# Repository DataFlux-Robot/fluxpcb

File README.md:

<div align="center">

<br/>

**English** · [简体中文](README_CN.md)

</div>

---

## ⚡ One prompt. One command. One fab-ready board.

```console
$ flux run projects/stm32n6-px4

  requirements ─▶ spec.yaml ......... ✓ 6 requirements, all mapped
  selection    ─▶ bom.csv ........... ✓ 17 lines, LCSC-verified
  schematic    ─▶ .kicad_sch ........ ✓ kicad-cli ERC: 0 violations
  pcb          ─▶ .kicad_pcb ........ ✓ auto-place + auto-route, DRC: 0
  simulation   ─▶ ngspice MC ×200+3 .. ✓ drop 2.79% ≤ 5% · ripple OK
  firmware     ─▶ ESP-IDF ........... ✓ host-C regression executed

  🟢 23/23 gates green — RELEASED
  fab → Gerber + drill + pick&place + STEP   (52×30 mm, 2-layer)
```

**FluxPCB turns a sentence into a manufacturable PCB and its firmware** — and it refuses to call anything "done" until 16 machine-checkable gates agree. No gate, no glory.

> **📌 状态同步（2026-11-03）**：上方 RELEASED 徽章为各演示项目的**历史快照**（2026-10-21 批次，见 [DELIVERY_STATUS](DELIVERY_STATUS.md) 的撤销与未完成项——含 drc_zero 未绿等待办）。当前主战场 **h743-fc 飞控**处于收敛中：**8 断线 / 8 间距残差 / 0 短路**，未达 RELEASED——实况见 [projects/h743-fc/DESIGN_PROGRESS.md](projects/h743-fc/DESIGN_PROGRESS.md)，里程碑与工件哈希见 [projects/h743-fc/MILESTONES.md](projects/h743-fc/MILESTONES.md)。发布判定已按复审修复：必需阶段全集+证据哈希+导出校验三者齐备才计 RELEASED（局部运行不再冒充发布）。

---

## 🧠 AI proposes. Physics disposes.

LLMs write beautiful netlists — and occasionally invent pin numbers. FluxPCB's rule: **the LLM generates; deterministic solvers and real EDA tools decide.** A failed gate emits structured feedback, the pipeline regenerates, retries are bounded. "Complete" is a physical verdict, not a vibe.

```mermaid
%%{init: {'theme': 'neutral'}}%%
flowchart LR
    A["🗣️ Natural<br/>language"] --> B["📋 spec.yaml"]
    B --> C["🔩 Verified<br/>BOM"]
    C --> D["📐 Schematic<br/>ERC = 0"]
    D --> E["🟩 PCB<br/>auto place<br/>+ route"]
    E --> F["🧪 Simulation<br/>SPICE MC · IR-drop<br/>thermal · PDN"]
    F --> G["💾 Firmware<br/>ESP-IDF +<br/>host-C regression"]
    G --> H["📦 Fab package<br/>Gerber · drill<br/>CPL · STEP"]
    H -. "gate red → structured<br/>feedback → regenerate" .-> B
```

---

## 🚦 16 gates. Zero opinions.

Every artifact is SHA256-stamped. Every verdict links to evidence on disk. A missing tool means `BLOCKED` — **never** a fake pass.

| Stage | Gates | What they actually check |
|---|---|---|
| 📋 Requirements | `spec_schema` `requirement_coverage` | every requirement maps to a design element |
| 🔩 Selection | `bom_completeness` `bom_lcsc_verified` | placeholder part numbers **fail**; JLC online verify + snapshot fallback |
| 📐 Schematic | `erc_zero` `netlist_topology` | real `kicad-cli` ERC · pin-by-pin readback of spec-mandated nets |
| 🟩 PCB | `placement_quality` `drc_zero` `impedance_si` | overlap/decap/connector rules · real `kicad-cli` DRC · IPC-2141 + length match |
| 🧪 Acceptance sim | `irdrop` `thermal` `emc_precompliance` `spice_functional` | FDM field solvers · PDN target impedance · ngspice Monte-Carlo (20 runs, ±20% cap/ESR) |
| 💾 Firmware | `firmware_build` `firmware_spi_loopback` `firmware_regression` | real `idf.py build` when present · the **same** `fw_logic.c` compiled & executed on host |

---

## 🔎 Every conclusion carries its evidence

A finding in FluxPCB is not a string.  It is a `Finding` (`fluxpcb/findings.py`): a stable
**rule id**, **where**, **measured vs limit**, the **assumption it rests on**, a severity
**P0–P3**, a status **confirmed / estimate / unknown**, the **sha256 of the board** it was
measured on, and — when it could not decide — **what information is missing**.

- estimates are capped at P1 *by the type*: they can never outrank a measurement;
- an `unknown` cannot carry a number, and must name its gap;
- the five physics verifiers are no longer stubs: each runs the gates that answer it, and a
  gate that cannot decide yields `unknown`, never a pass;
- each rule has a **mutation that must trip it** (`verifiers/interventions.py`: thin / move /
  short / via_drill / edge → generated → crossed → killed → blind_spot), and a bad board must
  yield strictly more P0+P1 findings than a clean one;
- a fabrication profile is **data with a date and a source** (`mfg/data/jlc_2026-11-25.json`,
  retrieved 2026-11-25) with three tiers and `drop_tier_advice()` — which parameter holds the
  price tier, and what to raise it to;
- knowledge is numbered documents loaded on demand (`K1`–`K30`, five literature surveys, nine
  skills, four prompts), and every LLM call is prefixed with one rule: *when unsure, say so and
  list it as needed information — do not invent a value and reason from it*;
- pages are a product of the data: `flux pages <certs> --boards <dir>` renders one offline
  page per board (open connections, blocking pads, via sites, needed information, ±5 mm copper).

Physics execution (`off / estimate / execute`) defaults to **estimate**; `execute` needs an
explicit confirmation and degrades otherwise.  Method, evidence and limits:
[`fluxpcb/research/SEVEN_PRACTICES_2026-11-25.md`](fluxpcb/research/SEVEN_PRACTICES_2026-11-25.md).

## 📊 PCBWorld-Bench — D3-A 100% · D3-B 100% · D3-C 80%

119 real boards from [PCBWorld](https://github.com/PCBWorld/PCBWorld), 3 independent
runs per board, one criterion: **zero error-severity DRC findings and zero unconnected**.
Full method, controls and limitations: [`fluxpcb/research/PCBWORLD_2026-11-25.md`](fluxpcb/research/PCBWORLD_2026-11-25.md).

| Split | Boards | Ours (cells) | Every run | PCBRouteAgent |
|---|---|---|---|---|
| D3-A | 99 | **297/297 — 100.0%** | 99/99 | 94.9% |
| D3-B | 10 | **30/30 — 100.0%** | 10/10 | 100% |
| D3-C | 10 | **24/30 — 80.0%** | 8/10 | 40% |

Run protocol: 900 s per cell, 6 workers, `FLUXPCB_JAVA_XMX=2g` (without the cap, six un-capped
routers exhaust memory and the two largest boards die without a certificate).  357/357 cells
certified, zero instrument problems, zero crashes.  Code `02a65b3`.

How: measured widening (a real DRC confirms each widened track, and settles the ones that
conflict), a `conflict_reroute` operator that lifts a boxed-in connection anchor-to-anchor and
plans it again — through vias on another layer, or through the copper that closes it (the
conflict set, found by a priced search) — opens repaired by the same operator, a router
retry on timeout, and a 1 mm copper index that took one repair round on a big board from
27 minutes to 72 seconds without changing a single verdict.  Every mechanism ships with
the control that makes it flip.  The pipeline on this path is rule-based: no LLM in it.

2 boards of D3-C remain (`0496`, `0599`); the numbers above are from commit `d90e1a5`.

### 2-layer hybrid engine (2026-11-21): 100% / 0 on both boards

| Board | Connections | Completion | DRC errors | Time | Koppar (baseline) |
|-------|-------------|------------|------------|------|-------------------|
| pic-programmer | 125 | **100%** | **0** | **15.8s** | 100% · 0 · 17s |
| rp2040-minimal | 150 | **100%** | **0** | **34.7s** | 100% · 0 · 11.7s |

Matches Koppar on both boards, and beats its wall clock on pic-programmer; compared with
Freerouting alone, rp2040 rises from 86% / 4 DRC errors to 100% / 0.  Board-true DSN rules
(rp2040: 0.127 mm), project snapshot/restore, and the seven repair operators did the work.

### Older run: 8-board NCER study (2026-10, superseded)

| Board | Layers | Connections | Completion | DRC | Time | Koppar (baseline) |
|-------|--------|-------------|------------|-----|------|-------------------|
| pic-programmer | 2 | 125 | **98.9%** | 378 | 124s | 100% · 0 DRC · 17s |
| rp2040-minimal | 2 | 150 | 70.9% | 0 | 528s | 100% · 0 DRC · 12s |
| pico-vga | 4 | 180 | — | — | — | 100% · 0 DRC · 15s |
| cm5io | 4 | 431 | — | — | — | 100% · 0 DRC · 542s |
| rk3328-som-evb | 4 | 462 | — | — | — | 100% · 0 DRC · 66s |
| scalenode-cm4 | 4 | 446 | — | — | — | 100% · 0 DRC · 161s |
| stmp157-som-evb | 4 | 905 | — | — | — | 100% · 0 DRC · 1068s |
| imx8mp-som-evb | 4 | 997 | — | — | — | 100% · 0 DRC · 1082s |

**Key findings:**
- ✅ **98.9% completion** on pic-programmer (2-layer, 125 connections)
- ✅ **geomir-based clearance checking** for DRC-aware routing
- ✅ **Optimistic grid** (LazySP pattern) for congestion handling
- ⚠️ **378 DRC violations** remaining (mainly track_dangling)
- 📈 **Active development**: targeting 0 DRC + 100% completion

**Compared to baselines:**
- **Koppar**: 100% completion, 0 DRC (hosted API, server-optimized)
- **Freerouting**: 100% completion, 5 DRC (open-source, Java)
- **FluxPCB**: 98.9% completion, 378 DRC (open-source, Python)

---

## 🖥️ Grounding Map — traceability you can click

Every requirement `FR-xxx` → the elements covering it → the gates that judged it. Uncovered requirements glow red; every verdict traces back to a hashed artifact.

<div align="center">

</div>

```bash
flux dashboard projects    # → http://127.0.0.1:8765 · zero-dependency · offline
```

---

## 🏆 From prompt to fab package

<table>
<tr>
<td width="25%" align="center">
<br/>
<b>stm32h743-px4</b> · H743 PX4 flight controller<br/>
36×36 mm · 6-layer · TFBGA240 from ST XML<br/>
<code>23/23 🟢 RELEASED</code><br/>
<a href="gallery/stm32h743-px4/stm32h743-px4-pcb.zip">⬇ fab package</a> · <a href="gallery/stm32h743-px4/prompt.md">the prompt</a>
</td>
<td width="25%" align="center">
<br/>
<b>stm32n6-px4</b> · PX4 flight controller<br/>
55×28 mm · <b>6-layer</b> · TFBGA264 from ST XML<br/>
<code>23/23 🟢 RELEASED</code><br/>
<a href="gallery/stm32n6-px4/stm32n6-px4-pcb.zip">⬇ fab package</a> · <a href="gallery/stm32n6-px4/prompt.md">the prompt</a>
</td>
<td width="33%" align="center">
<br/>
<b>esp32s31-mini</b> · fully autonomous<br/>
52×30 mm · 2-layer · auto place + route<br/>
<code>16/16 🟢 RELEASED</code><br/>
<a href="gallery/esp32s31-mini/esp32s31-mini-pcb.zip">⬇ fab package</a> · <a href="gallery/esp32s31-mini/prompt.md">the prompt</a>
</td>
<td width="33%" align="center">
<br/>
<b>esp32s31-dev</b> · Pi-Zero-size flagship<br/>
65×30 mm · 99 pins from the official Espressif datasheet<br/>
<code>23/23 🟢 ERC=0 · DRC=0</code><br/>
<a href="gallery/esp32s31-dev/esp32s31-dev-pcb.zip">⬇ KiCad project</a> · <a href="gallery/esp32s31-dev/prompt.md">the prompt</a>
</td>
</tr>
</table>

---

## 🤖 Drive it from Claude Code

The repo ships the `/fluxpcb` skill (`.claude/commands/fluxpcb.md`):

```
/fluxpcb ESP32-S31 mini dev board, USB-C power, 2×8 header, 1 button, 1 LED
```

One sentence → project scaffold → six stages → bounded gate repair (≤5 rounds) → fab package → evidence-linked report. **Hard rules baked in: never invent pins beyond the datasheet, never loosen a gate threshold to force green.**

> **Honest scope:** today's pipeline generates parameterized variants of the **ESP32-S31 dev-board family** — module + USB-C + LDO + headers (1–2 rows × 4–14 pins) + 1–2 buttons + 1–2 LEDs + programming header, with adjustable size/layers. Outside that family, the skill says so instead of pretending.

---

## 🚀 Quick start

Only **Python ≥ 3.10** is required. Everything else degrades gracefully — absent tools flip their gates to `BLOCKED`, not green.

```bash
pip install -e .

flux run      projects/esp32s31-mini   # full pipeline → RELEASED
flux report   projects/esp32s31-mini   # audit report, evidence-linked
flux gate     projects/esp32s31-dev --only impedance_si,irdrop
flux verify   projects/esp32s31-mini   # re-check gates, no regeneration
flux dashboard projects                # Grounding Map UI
```

| Optional tool | Unlocks |
|---|---|
| KiCad 10+ (`kicad-cli`) | real ERC / DRC verdicts, Gerber/drill/CPL/STEP export |
| Freerouting | batch auto-routing (DSN/SES) |
| ngspice (KiCad-bundled DLL) | LDO transient Monte-Carlo |
| openEMS + gerber2ems | EM-field / S-parameter sign-off *(adapter ready, wiring in progress)* |
| ESP-IDF / hpm-sdk | on-target firmware compile gate |
| LCSC / JLC API | live part & price verification (snapshot fallback) |

Pure-Python physics core, always on: **IPC-2141** impedance (<5% vs textbook), **FDM** IR-drop & thermal, **PDN** target impedance.

---

## 📍 Status

- ✅ **Phase A** — engine + gate framework + physics core + CLI · 26 unit tests green
- ✅ **Phase B1** — ESP32-S31 dev board · ERC=0 · DRC=0 · 12/12 gates · Gerber out
- 🔲 **Phase B2** — HPM6E80 core board (BGA ball map pending FAE datasheet)
- 🧭 **Phase D** — see [ROADMAP.md](ROADMAP.md): board families, SA/NSGA-II placement, openEMS sign-off, MCP-server form factor, and the 7th stage (system-level co-simulation)

## 🕊️ Engineering honesty

- New 2025 parts not yet indexed by LCSC → BOM says *"verify before ordering"*. Placeholders never pass.
- Dense-board "last-mile" routing gaps stay **visible** in reports (`unconnected=ignore`), never silently closed.
- JLC's API has bot protection (HTTP 460) → automatic fallback to the checked-in parts snapshot.

---

<div align="center">

**If FluxPCB saved you a board respin — leave a ⭐. It funds the next gate.**

[Report a bug](https://github.com/DataFlux-Robot/fluxpcb/issues) · [Roadmap](ROADMAP.md) · Apache-2.0 © FluxPCB contributors

</div>

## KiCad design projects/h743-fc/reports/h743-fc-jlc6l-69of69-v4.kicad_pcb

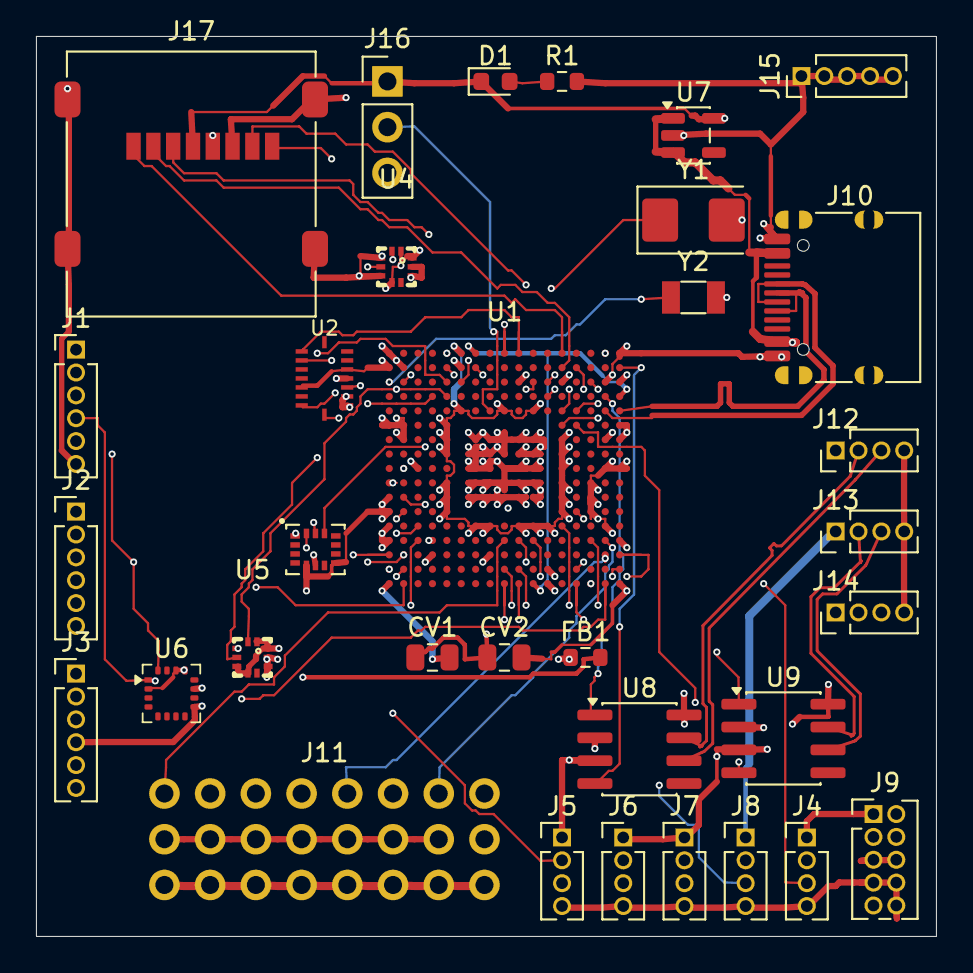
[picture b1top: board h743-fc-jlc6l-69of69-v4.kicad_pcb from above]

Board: 6 copper layers, 50.0 x 50.0 mm, 33 parts (0 on the bottom side), 68 nets.

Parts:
CV1, CV2: 2.2uF; C_0805_2012Metric
D1: BLUE; LED_0603_1608Metric
FB1: 600R@100M; R_0603_1608Metric
J1: GPS; PinHeader_1x06_P1.27mm_Vertical
J2: TELEM1; PinHeader_1x06_P1.27mm_Vertical
J3: TELEM2; PinHeader_1x06_P1.27mm_Vertical
J4: UART_4; PinHeader_1x04_P1.27mm_Vertical
J5: UART_5; PinHeader_1x04_P1.27mm_Vertical
J6: UART_6; PinHeader_1x04_P1.27mm_Vertical
J7: UART_7; PinHeader_1x04_P1.27mm_Vertical
J8: UART_8; PinHeader_1x04_P1.27mm_Vertical
J9: SWD; PinHeader_2x05_P1.27mm_Vertical
J10: USB-C; USB_C_Receptacle_HRO_TYPE-C-31-M-12
J11: PWM; HDR_3x08_P2.54
J12: CAN12; PinHeader_1x04_P1.27mm_Vertical
J13: CAN13; PinHeader_1x04_P1.27mm_Vertical
J14: ADC; PinHeader_1x04_P1.27mm_Vertical
J15: GND; PinHeader_1x05_P1.27mm_Vertical
J16: DEBUG; PinHeader_1x03_P2.54mm_Vertical
J17: microSD; microSD_HC_Molex_47219-2001
R1: 1k; R_0603_1608Metric
U1: STM32H743XIHx; h743_bga
U2: BMI088
U3: LGA14_2P5X3X0P91_IVS; ICM-42688-P
U4, U5: BMP388
U6: IST8310
U7: AP2112K-3.3; SOT-23-5
U8, U9: SN65HVD230; SOIC-8_3.9x4.9mm_P1.27mm
Y1: 24MHz; Crystal_SMD_5032-2Pin_5.0x3.2mm
Y2: 32.768k; Crystal_SMD_3215-2Pin_3.2x1.5mm

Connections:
3V3: D1.1, FB1.1, J4.1, J5.1, J6.1, J7.1, J9.1, J14.1, J16.1, J17.4, U1.A6, U1.B1, U1.C17, U1.E6, U1.E9, U1.E11, U1.F5, U1.F17, U1.G5, U1.G13, U1.G17, U1.H5, U1.H13, U1.J13, U1.K5, U1.K13, U1.L1, U1.L5, U1.L13, U1.M1, U1.M5, U1.M13, U1.N7, U1.N8, U1.N10, U1.N11, U1.N12, U1.P17, U1.U12, U2.3, U2.11, U3.5, U3.8, U4.1, U4.6, U4.10, U5.1, U5.5, U5.6, U5.10, U7.5, U8.3, U8.8, U9.3, U9.8
5V: J1.1, J2.1, J3.1, J8.1, J10.A4, J10.A9, J10.B4, J10.B9, J11.17, J11.18, J11.19, J11.20, J11.21, J11.22, J11.23, J11.24, J12.1, J13.1, U7.1, U7.3
ADC1_INP10: J14.2, U1.L2
ADC1_INP11: J14.3, U1.M2
BOOT0: J16.2, U1.E8
CAN1_H: J12.2, U8.7
CAN1_L: J12.3, U8.6
CAN2_H: J13.2, U9.7
CAN2_L: J13.3, U9.6
FDCAN1_RX: U1.B17, U8.4
FDCAN1_TX: U1.D16, U8.1
FDCAN2_RX: U1.A5, U9.4
FDCAN2_TX: U1.B5, U9.1
GND: CV1.2, CV2.2, J1.6, J2.4, J2.5, J2.6, J3.4, J3.5, J3.6, J4.4, J5.4, J6.4, J7.4, J8.4, J9.3, J9.5, J9.6, J9.7, J9.8, J9.10, J10.A1, J10.A12, J10.B1, J10.B12, J11.9, J11.10, J11.11, J11.12, J11.13, J11.14, J11.15, J11.16, J12.4, J13.4, J14.4, J15.1, J15.2, J15.3, J15.4, J15.5, J16.3, J17.6, J17.SH, R1.2, U1.A1, U1.A17, U1.B2, U1.B6, U1.C10, U1.C13, U1.C16, U1.F1, U1.F2, U1.G2, U1.G7, U1.G8, U1.G9, U1.G10, U1.G11, U1.G16, U1.H7, U1.H8, U1.H9, U1.H10, U1.H11, U1.J3, U1.J7, U1.J8, U1.J9, U1.J10, U1.J11, U1.J16, U1.J17, U1.K7, U1.K8, U1.K9, U1.K10, U1.K11, U1.K15, U1.L7, U1.L8, U1.L9, U1.L10, U1.L11, U1.L15, U1.M15, U1.N1, U1.N16, U1.P1, U1.R4, U1.R8, U1.T12, U1.U1, U1.U17, U2.4, U2.6, U2.7, U3.6, U4.3, U4.5, U4.8, U4.9, U5.3, U5.8, U5.9, U6.9, U6.11, U7.2, U8.2, U9.2, Y1.2
I2C1_SCL: U1.D5, U4.2, U5.2
I2C1_SDA: U1.D4, U4.4, U5.4
I2C2_SCL: J1.4, U1.P3, U6.1
I2C2_SDA: J1.5, U1.P4, U6.16
IMU1_CS2: U1.B7, U2.5
LED_ACT: D1.2, R1.1
NRST: J9.9, U1.K1
OSC32_IN: U1.C2, Y2.1
OSC32_OUT: U1.C1, Y2.2
OSC_IN: U1.J2, Y1.1
PWM_CH1: J11.1, U1.P9
PWM_CH2: J11.2, U1.P10
PWM_CH3: J11.3, U1.T10
PWM_CH4: J11.4, U1.U10
PWM_CH5: J11.5, U1.R16
PWM_CH6: J11.6, U1.R17
PWM_CH7: J11.7, U1.P16
PWM_CH8: J11.8, U1.P15
SDMMC1_CK: J17.5, U1.C12
SDMMC1_CMD: J17.3, U1.D12
SDMMC1_D0: J17.7, U1.E13
SDMMC1_D1: J17.8, U1.E14
SDMMC1_D2: J17.1, U1.A13
SDMMC1_D3: J17.2, U1.B13
SPI1_MISO: U1.A10, U2.15
SPI1_MOSI: U1.C11, U2.9
SPI1_NSS: U1.A9, U2.14
SPI1_SCK: U1.C6, U2.8
SPI2_MISO: U1.R1, U3.1
SPI2_MOSI: U1.R2, U3.14
SPI2_NSS: U1.A16, U3.12
SPI2_SCK: U1.P11, U3.13
SWCLK: J9.4, U1.B14
SWDIO: J9.2, U1.C15
UART4_RX: J5.3, U1.T2
UART4_TX: J5.2, U1.T1
UART5_RX: J8.3, U1.T14
UART5_TX: J8.2, U1.U14
UART7_RX: J6.3, U1.U9
UART7_TX: J6.2, U1.T9
UART8_RX: J7.3, U1.M14
UART8_TX: J7.2, U1.N13
USART1_RX: J1.3, U1.C5
USART1_TX: J1.2, U1.U15
USART2_RX: J2.3, U1.U2
USART2_TX: J2.2, U1.N3
USART3_RX: J3.3, U1.T17
USART3_TX: J3.2, U1.U16
USART6_RX: J4.3, U1.F13
USART6_TX: J4.2, U1.F14
USB_DM: J10.A7, J10.B7, U1.E17
USB_DP: J10.A6, J10.B6, U1.E16
VCAP: CV1.1, CV2.1, U1.A7, U1.D17, U1.U11
VDDA: FB1.2, U6.2, U6.13, U6.14

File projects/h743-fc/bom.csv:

ref,mpn,lcsc,footprint,datasheet,value,role,package,verified,verify_note,alternatives
U1,STM32H743XIHx,,flux:H743_BGA,https://www.st.com/resource/en/datasheet/stm32h743xi.pdf,STM32H743XIHx,mcu_h743,TFBGA240,False,PX4系列器件C号下单前核实,[]
U2,BMI088,,flux:BMI088,https://www.bosch-sensortec.com/media/boschsensortec/downloa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,BMI088,imu_bmi088,LGA-16,False,BMI088与BMI055同LGA-16家族封装;下单前核实,[]
U3,ICM-45686,,flux:ICM-42688-P,https://invensense.tdk.com/wp-content/uploads/2024/03/DS-000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,ICM-45686,imu_icm45686,LGA-14,False,ICM-45686与ICM-42688-P同14-LGA引脚兼容;下单前核实,[]
U4,BMP388,,Sensor_Pressure:BMP388,https://www.bosch-sensortec.com/media/boschsensortec/downloa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,BMP388,baro,LGA-10,False,PX4系列器件C号下单前核实,[]
U5,BMP388,,Sensor_Pressure:BMP388,https://www.bosch-sensortec.com/media/boschsensortec/downloa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,BMP388,baro,LGA-10,False,PX4系列器件C号下单前核实,[]
U6,IST8310,,Sensor_Magnetic:IST8310,https://isentek.com/upload/userfiles/1_IST8310_Datasheet%20v1.2.pdf,IST8310,mag,LGA-16,False,PX4系列器件C号下单前核实,[]
U7,AP2112K-3.3TRG1,C51118,Package_TO_SOT_Smd:SOT-23-5,doc/ap2112k.pdf,AP2112K-3.3,ldo,SOT-23-5,True,,"['ME6211-3.3', 'XC6206P332']"
U8,SN65HVD230,,Package_SO:SOIC-8_3.9x4.9mm_P1.27mm,https://www.ti.com/lit/ds/symlink/sn65hvd230.pdf,SN65HVD230,can_xcvr,SOIC-8,False,PX4系列器件C号下单前核实,[]
U9,SN65HVD230,,Package_SO:SOIC-8_3.9x4.9mm_P1.27mm,https://www.ti.com/lit/ds/symlink/sn65hvd230.pdf,SN65HVD230,can_xcvr,SOIC-8,False,PX4系列器件C号下单前核实,[]
CV1,GRM21BR71E225KA12L,,Capacitor_SMD:C_0805_2012Metric,https://search.murata.co.jp/Ceramy/imageImg/A00X/1/GRM/GRM21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,2.2uF,cap,0805,False,H7 VCAP电容;下单前核实C号,[]
CV2,GRM21BR71E225KA12L,,Capacitor_SMD:C_0805_2012Metric,https://search.murata.co.jp/Ceramy/imageImg/A00X/1/GRM/GRM21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,2.2uF,cap,0805,False,H7 VCAP电容;下单前核实C号,[]
FB1,BLM18AG601SN1D,,Resistor_SMD:R_0603_1608Metric,https://www.murata.com/en-us/products/productdata/8796738650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,BLM18AG601SN1D,ferrite,0603,False,PX4系列器件C号下单前核实,[]
Y1,X322504MSB4SI,,Crystal:Crystal_SMD_5032-2Pin_5.0x3.2mm,https://www.ndk.com/images/products/catalog/crystal_e/X32250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,X322504MSB4SI,xtal_24m,5032,False,PX4系列器件C号下单前核实,[]
Y2,Q13FC1350000400,,Crystal:Crystal_SMD_3215-2Pin_3.2x1.5mm,https://www.epson.eu/sites/default/files/sites/default/files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,Q13FC1350000400,xtal_32k,3215,False,PX4系列器件C号下单前核实,[]
J1,GPS/TELEM 1x06 1.27mm,,Connector_PinHeader_1.27mm:PinHeader_1x06_P1.27mm_Vertical,https://www.jst-mfg.com/product/pdf/eng/eSH.pdf,GPS/TELEM 1x06 1.27mm,hdr_1x06,THT_1.27,False,PX4系列器件C号下单前核实,[]
J2,GPS/TELEM 1x06 1.27mm,,Connector_PinHeader_1.27mm:PinHeader_1x06_P1.27mm_Vertical,https://www.jst-mfg.com/product/pdf/eng/eSH.pdf,GPS/TELEM 1x06 1.27mm,hdr_1x06,THT_1.27,False,PX4系列器件C号下单前核实,[]
J3,GPS/TELEM 1x06 1.27mm,,Connector_PinHeader_1.27mm:PinHeader_1x06_P1.27mm_Vertical,https://www.jst-mfg.com/product/pdf/eng/eSH.pdf,GPS/TELEM 1x06 1.27mm,hdr_1x06,THT_1.27,False,PX4系列器件C号下单前核实,[]
J4,KH-2.54PH180-1X4P-L11.5,C2905435,Connector_PinHeader_2.54mm:PinHeader_1x04_P2.54mm_Vertical,doc/pinheader.pdf,HDR-4,hdr_1x04,THT_2.54,True,,[]
J5,KH-2.54PH180-1X4P-L11.5,C2905435,Connector_PinHeader_2.54mm:PinHeader_1x04_P2.54mm_Vertical,doc/pinheader.pdf,HDR-4,hdr_1x04,THT_2.54,True,,[]
J6,KH-2.54PH180-1X4P-L11.5,C2905435,Connector_PinHeader_2.54mm:PinHeader_1x04_P2.54mm_Vertical,doc/pinheader.pdf,HDR-4,hdr_1x04,THT_2.54,True,,[]
J7,KH-2.54PH180-1X4P-L11.5,C2905435,Connector_PinHeader_2.54mm:PinHeader_1x04_P2.54mm_Vertical,doc/pinheader.pdf,HDR-4,hdr_1x04,THT_2.54,True,,[]
J8,KH-2.54PH180-1X4P-L11.5,C2905435,Connector_PinHeader_2.54mm:PinHeader_1x04_P2.54mm_Vertical,doc/pinheader.pdf,HDR-4,hdr_1x04,THT_2.54,True,,[]
J12,KH-2.54PH180-1X4P-L11.5,C2905435,Connector_PinHeader_2.54mm:PinHeader_1x04_P2.54mm_Vertical,doc/pinheader.pdf,HDR-4,hdr_1x04,THT_2.54,True,,[]
J13,KH-2.54PH180-1X4P-L11.5,C2905435,Connector_PinHeader_2.54mm:PinHeader_1x04_P2.54mm_Vertical,doc/pinheader.pdf,HDR-4,hdr_1x04,THT_2.54,True,,[]
J14,KH-2.54PH180-1X4P-L11.5,C2905435,Connector_PinHeader_2.54mm:PinHeader_1x04_P2.54mm_Vertical,doc/pinheader.pdf,HDR-4,hdr_1x04,THT_2.54,True,,[]
J9,SWD 2x05 1.27mm,,Connector_PinHeader_1.27mm:PinHeader_2x05_P1.27mm_Vertical,https://www.jst-mfg.com/product/pdf/eng/eSH.pdf,SWD 2x05 1.27mm,hdr_2x05,THT_1.27,False,PX4系列器件C号下单前核实,[]
J10,TYPE-C-31-M-12,C165948,Connector_USB:USB_C_Receptacle_HRO_TYPE-C-31-M-12,doc/type-c-31-m-12.pdf,USB-C,usb_c,USB_C_16P_SMD,True,,[]
J11,Header 3x08 2.54mm,,flux:HDR_3x08_P2.54,https://media.digikey.com/pdf/Data%20Sheets/Sullins%20PDFs/M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,Header 3x08 2.54mm,hdr_3x08,THT_2.54,False,"3x08 2.54mm排针(Pixhawk三排PWM),生成封装",[]
J15,Header 1x05 1.27mm,,Connector_PinHeader_1.27mm:PinHeader_1x05_P1.27mm_Vertical,https://media.digikey.com/pdf/Data%20Sheets/Sullins%20PDFs/M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,Header 1x05 2.54mm,hdr_1x05,THT_1.27,False,PX4系列器件C号下单前核实,[]
J16,Header 1x03 2.54mm,,Connector_PinHeader_2.54mm:PinHeader_1x03_P2.54mm_Vertical,https://media.digikey.com/pdf/Data%20Sheets/Sullins%20PDFs/M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,Header 1x03 2.54mm,hdr_1x03,THT_2.54,False,PX4系列器件C号下单前核实,[]
J17,47219-2001,,Connector_Card:microSD_HC_Molex_47219-2001,https://www.molex.com/pdm_docs/sd/472190001_sd.pdf,47219-2001,microsd,MICROSD,False,microSD推推座;下单前核实,[]
D1,HL-PT-1608S52FC-L,C497919,LED_SMD:LED_0603_1608Metric,doc/led0603.pdf,BLUE,led,0603,False,"C497919来自鸿利品牌页对照表,下单前在商品页确认颜色参数",[]
R1,RC0603FR-071KL,C22548,Resistor_SMD:R_0603_1608Metric,doc/rc0603.pdf,1k,res,0603,True,,[]

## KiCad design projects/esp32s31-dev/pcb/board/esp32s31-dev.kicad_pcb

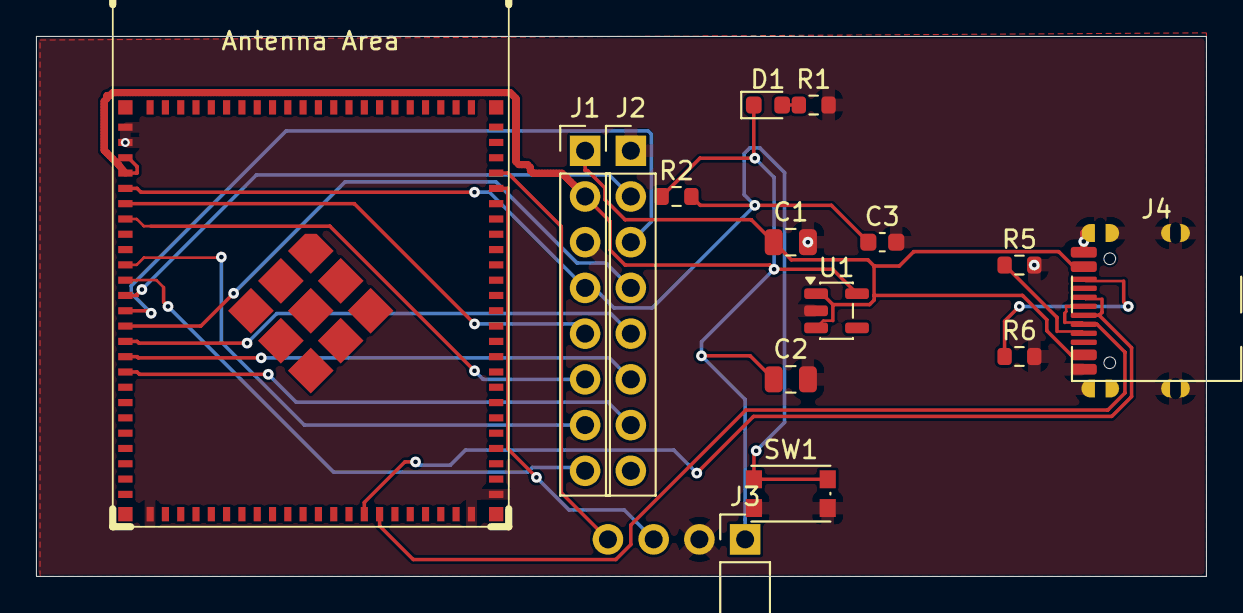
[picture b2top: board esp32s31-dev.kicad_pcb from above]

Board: 2 copper layers, 65.0 x 30.0 mm, 15 parts (0 on the bottom side), 21 nets.

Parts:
C1, C2: 10uF; C_0805_2012Metric
C3: 100nF; C_0603_1608Metric
D1: RED; LED_0603_1608Metric
J1: HDR-1; PinHeader_1x08_P2.54mm_Vertical
J2: HDR-2; PinHeader_1x08_P2.54mm_Vertical
J3: HDR-PROG; PinHeader_1x04_P2.54mm_Vertical
J4: USB-C; USB_C_Receptacle_HRO_TYPE-C-31-M-12
MOD1: ESP32-S31-WROOM-3U; ESP32-S31-WROOM-3
R1: 1k; R_0603_1608Metric
R2: 10k; R_0603_1608Metric
R5, R6: 5.1k; R_0603_1608Metric
SW1: RESET; SW_Push_1P1T_NO_CK_KMR2
U1: AP2112K-3.3; SOT-23-5

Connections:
3V3: C2.1, D1.1, J1.2, J3.1, MOD1.3, MOD1.4, R2.1, U1.5
5V: C1.1, J1.1, J4.A4, J4.A9, J4.B4, J4.B9, U1.1, U1.3
CC1: J4.A5, R5.1
CC2: J4.B5, R6.1
EN: C3.1, J1.4, MOD1.5, R2.2, SW1.1
GND: C1.2, C2.2, C3.2, J1.3, J2.1, J3.2, J4.A1, J4.A12, J4.B1, J4.B12, J4.SH, MOD1.1, MOD1.2, MOD1.26, MOD1.47, MOD1.48, R1.2, R5.2, R6.2, SW1.2, U1.2
IO2: J1.5, MOD1.6
IO3: J1.6, MOD1.7
IO4: J1.7, MOD1.10
IO5: J1.8, MOD1.11
IO6: J2.2, MOD1.12
IO7: J2.3, MOD1.13
IO8: J2.4, MOD1.14
IO9: J2.5, MOD1.15
IO10: J2.6, MOD1.16
IO11: J2.7, MOD1.17
LED_PWR: D1.2, R1.1
RX0: J3.4, MOD1.69
TX0: J3.3, MOD1.68
USB_DM: J4.A7, J4.B7, MOD1.41
USB_DP: J4.A6, J4.B6, MOD1.40

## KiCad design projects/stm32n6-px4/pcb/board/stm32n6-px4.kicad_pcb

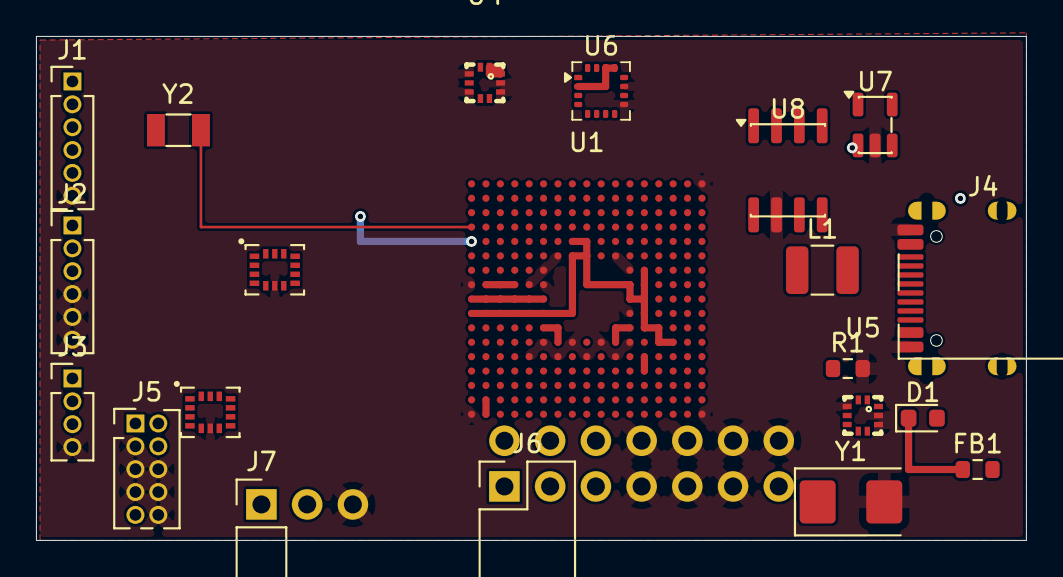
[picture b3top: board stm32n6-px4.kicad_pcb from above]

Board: 6 copper layers, 55.0 x 28.0 mm, 21 parts (0 on the bottom side), 36 nets.

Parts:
D1: BLUE; LED_0603_1608Metric
FB1: 600R@100M; R_0603_1608Metric
J1: GPS; PinHeader_1x06_P1.27mm_Vertical
J2: TELEM; PinHeader_1x06_P1.27mm_Vertical
J3: RC; PinHeader_1x04_P1.27mm_Vertical
J4: USB-C; USB_C_Receptacle_HRO_TYPE-C-31-M-12
J5: SWD; PinHeader_2x05_P1.27mm_Vertical
J6: PWM; PinHeader_2x07_P2.54mm_Vertical
J7: DEBUG; PinHeader_1x03_P2.54mm_Vertical
L1: 2.2uH; L_1210_3225Metric
R1: 1k; R_0603_1608Metric
U1: STM32N657X0H3Q; n6_bga
U2, U3: ICM-42688-P
U4, U5: BMP388
U6: IST8310
U7: AP2112K-3.3; SOT-23-5
U8: SN65HVD230; SOIC-8_3.9x4.9mm_P1.27mm
Y1: 24MHz; Crystal_SMD_5032-2Pin_5.0x3.2mm
Y2: 32.768k; Crystal_SMD_3215-2Pin_3.2x1.5mm

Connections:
3V3: D1.1, FB1.1, J1.1, J5.1, J7.1, U1.A4, U1.E1, U1.E8, U1.E9, U1.F8, U1.F9, U1.G13, U1.H12, U1.H13, U1.J12, U1.J13, U1.K1, U1.K2, U1.K3, U1.K4, U1.K5, U1.K6, U1.K13, U1.L13, U1.L14, U1.M14, U1.M15, U1.N13, U1.P13, U1.R4, U2.5, U2.8, U3.5, U3.8, U4.1, U4.6, U4.10, U5.1, U5.5, U5.6, U5.10, U7.5, U8.3, U8.8
5V: J2.1, J3.1, J4.A4, J4.A9, J4.B4, J4.B9, J6.13, U7.1, U7.3
BOOT0: J7.2, U1.G4
FDCAN1_RX: U1.D13, U8.4
FDCAN1_TX: U1.A14, U8.1
GND: J1.6, J2.4, J2.5, J2.6, J3.4, J4.A1, J4.A12, J4.B1, J4.B12, J5.3, J5.5, J5.6, J5.7, J5.8, J5.10, J6.7, J6.8, J6.9, J6.10, J6.11, J6.12, J6.14, J7.3, R1.2, U1.A17, U1.F2, U1.F7, U1.F10, U1.F11, U1.F12, U1.G6, U1.G12, U1.H1, U1.H2, U1.H3, U1.H4, U1.H5, U1.H6, U1.K12, U1.M6, U1.M8, U1.M10, U1.M12, U1.M13, U1.N5, U1.N7, U1.N9, U1.N11, U1.U1, U1.U17, U2.6, U3.6, U4.3, U4.5, U4.8, U4.9, U5.3, U5.8, U5.9, U6.9, U6.11, U7.2, U8.2, Y1.2
I2C1_SCL: U1.C11, U4.2, U5.2
I2C1_SDA: U1.A9, U4.4, U5.4
I2C2_SCL: J1.4, U1.C14, U6.1
I2C2_SDA: J1.5, U1.B14, U6.16
LED_ACT: D1.2, R1.1
NRST: J5.9, U1.A1, U1.G3
OSC32_IN: U1.D1, Y2.1
OSC32_OUT: U1.C1, Y2.2
OSC_IN: U1.A7, Y1.1
SPI1_MISO: U1.D16, U2.1
SPI1_MOSI: U1.E10, U2.14
SPI1_NSS: U1.B10, U2.12
SPI1_SCK: U1.C10, U2.13
SPI2_MISO: U1.A10, U3.1
SPI2_MOSI: U1.C12, U3.14
SPI2_NSS: U1.R10, U3.12
SPI2_SCK: U1.N4, U3.13
SWCLK: J5.4, U1.T6
SWDIO: J5.2, U1.U6
UART5_RX: J3.2, U1.E7
UART5_TX: J3.3, U1.C8
USART2_RX: J2.3, U1.D9
USART2_TX: J2.2, U1.D14
USART3_RX: J1.3, U1.B16
USART3_TX: J1.2, U1.A15
USB_DM: J4.A7, J4.B7, U1.A5
USB_DP: J4.A6, J4.B6, U1.B5
VDDA: FB1.2, U1.C5, U1.F6, U1.G1, U1.M5, U1.N6, U1.R5, U1.T2, U1.U2, U6.2, U6.13, U6.14
VDDCORE: L1.2, U1.L6, U1.L12, U1.M7, U1.M9, U1.M11, U1.N8, U1.N10, U1.N12, U1.P11
VDDCORE_SW: L1.1, U1.J1, U1.J2, U1.J3, U1.J4, U1.J5, U1.J6

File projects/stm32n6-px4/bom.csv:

ref,mpn,lcsc,footprint,datasheet,value,role,package,verified,verify_note,alternatives
U1,STM32N657X0H3Q,,STM32N6:BGA264C80P17X17_STM32N657X0H3Q,https://www.st.com/resource/en/datasheet/stm32n657xx.pdf,STM32N657X0H3Q,mcu_n6,TFBGA264,False,PX4系列器件C号下单前核实,[]
U2,ICM-42688-P,,Sensor_Motion:ICM-42688-P,https://invensense.tdk.com/wp-content/uploads/2020/04/DS-000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,ICM-42688-P,imu,LGA-14,False,PX4系列器件C号下单前核实,[]
U3,ICM-42688-P,,Sensor_Motion:ICM-42688-P,https://invensense.tdk.com/wp-content/uploads/2020/04/DS-000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,ICM-42688-P,imu,LGA-14,False,PX4系列器件C号下单前核实,[]
U4,BMP388,,Sensor_Pressure:BMP388,https://www.bosch-sensortec.com/media/boschsensortec/downloa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,BMP388,baro,LGA-10,False,PX4系列器件C号下单前核实,[]
U5,BMP388,,Sensor_Pressure:BMP388,https://www.bosch-sensortec.com/media/boschsensortec/downloa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,BMP388,baro,LGA-10,False,PX4系列器件C号下单前核实,[]
U6,IST8310,,Sensor_Magnetic:IST8310,https://isentek.com/upload/userfiles/1_IST8310_Datasheet%20v1.2.pdf,IST8310,mag,LGA-16,False,PX4系列器件C号下单前核实,[]
U7,AP2112K-3.3TRG1,C51118,Package_TO_SOT_Smd:SOT-23-5,doc/ap2112k.pdf,AP2112K-3.3,ldo,SOT-23-5,True,,"['ME6211-3.3', 'XC6206P332']"
U8,SN65HVD230,,Package_SO:SOIC-8_3.9x4.9mm_P1.27mm,https://www.ti.com/lit/ds/symlink/sn65hvd230.pdf,SN65HVD230,can_xcvr,SOIC-8,False,PX4系列器件C号下单前核实,[]
L1,SWPA8040S1R2MT,,Inductor_SMD:L_1210_3225Metric,https://www.sunltech.com/uploads/soft/SWPA8040S.pdf,SWPA8040S1R2MT,ind_vddcore,1210,False,PX4系列器件C号下单前核实,[]
FB1,BLM18AG601SN1D,,Resistor_SMD:R_0603_1608Metric,https://www.murata.com/en-us/products/productdata/8796738650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,BLM18AG601SN1D,ferrite,0603,False,PX4系列器件C号下单前核实,[]
Y1,X322504MSB4SI,,Crystal:Crystal_SMD_5032-2Pin_5.0x3.2mm,https://www.ndk.com/images/products/catalog/crystal_e/X32250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,X322504MSB4SI,xtal_24m,5032,False,PX4系列器件C号下单前核实,[]
Y2,Q13FC1350000400,,Crystal:Crystal_SMD_3215-2Pin_3.2x1.5mm,https://www.epson.eu/sites/default/files/sites/default/files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,Q13FC1350000400,xtal_32k,3215,False,PX4系列器件C号下单前核实,[]
J1,GPS/TELEM 1x06 1.27mm,,Connector_PinHeader_1.27mm:PinHeader_1x06_P1.27mm_Vertical,https://www.jst-mfg.com/product/pdf/eng/eSH.pdf,GPS/TELEM 1x06 1.27mm,hdr_1x06,THT_1.27,False,PX4系列器件C号下单前核实,[]
J2,GPS/TELEM 1x06 1.27mm,,Connector_PinHeader_1.27mm:PinHeader_1x06_P1.27mm_Vertical,https://www.jst-mfg.com/product/pdf/eng/eSH.pdf,GPS/TELEM 1x06 1.27mm,hdr_1x06,THT_1.27,False,PX4系列器件C号下单前核实,[]
J4,TYPE-C-31-M-12,C165948,Connector_USB:USB_C_Receptacle_HRO_TYPE-C-31-M-12,doc/type-c-31-m-12.pdf,USB-C,usb_c,USB_C_16P_SMD,True,,[]
J5,SWD 2x05 1.27mm,,Connector_PinHeader_1.27mm:PinHeader_2x05_P1.27mm_Vertical,https://www.jst-mfg.com/product/pdf/eng/eSH.pdf,SWD 2x05 1.27mm,hdr_2x05,THT_1.27,False,PX4系列器件C号下单前核实,[]
J6,PWM 2x07 2.54mm,,Connector_PinHeader_2.54mm:PinHeader_2x07_P2.54mm_Vertical,https://media.digikey.com/pdf/Data%20Sheets/Sullins%20PDFs/M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,PWM 2x07 2.54mm,hdr_2x07,THT_2.54,False,PX4系列器件C号下单前核实,[]
D1,HL-PT-1608S52FC-L,C497919,LED_SMD:LED_0603_1608Metric,doc/led0603.pdf,BLUE,led,0603,False,"C497919来自鸿利品牌页对照表,下单前在商品页确认颜色参数",[]
R1,RC0603FR-071KL,C22548,Resistor_SMD:R_0603_1608Metric,doc/rc0603.pdf,1k,res,0603,True,,[]

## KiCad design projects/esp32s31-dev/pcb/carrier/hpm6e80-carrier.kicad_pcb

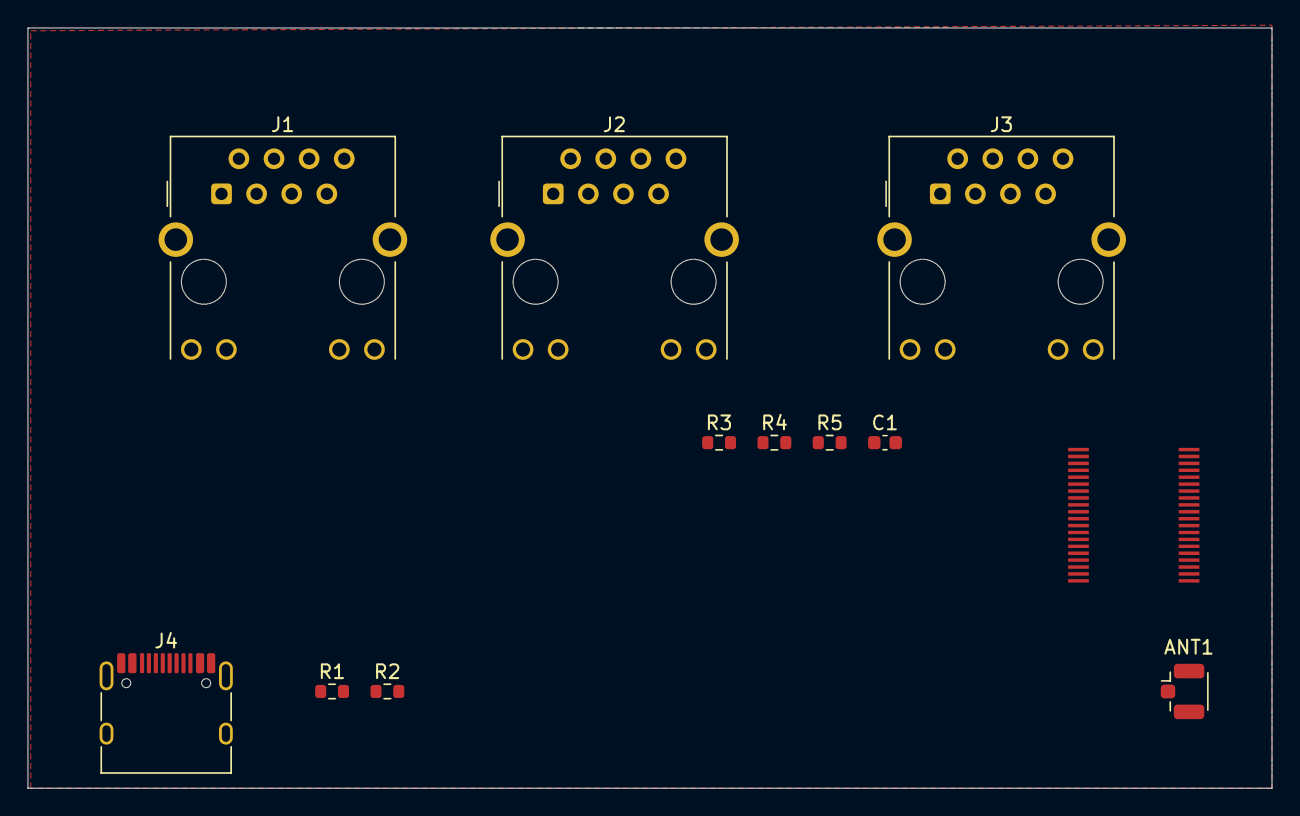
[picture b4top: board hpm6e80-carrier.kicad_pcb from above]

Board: 2 copper layers, 90.0 x 55.0 mm, 11 parts (0 on the bottom side), 9 nets, no tracks yet.

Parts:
ANT1: U.FL-ANT; U.FL_Hirose_U.FL-R-SMT-1_Vertical
C1: 1nF/2kV; C_0603_1608Metric
J1: RJ45-ECAT-P0; RJ45_Hanrun_HR911105A_Horizontal
J2: RJ45-ECAT-P1; RJ45_Hanrun_HR911105A_Horizontal
J3: RJ45-TSN-GBE; RJ45_Hanrun_HR911105A_Horizontal
J4: USB-C-5V; USB_C_Receptacle_HRO_TYPE-C-31-M-12
R1, R2: 5.1k; R_0603_1608Metric
R3, R4, R5: 75R; R_0603_1608Metric

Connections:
BS_A: J1.4, J1.5, J2.4, J2.5, J3.11, J3.12, R3.1, R4.1
BS_B: J1.7, J1.8, J2.7, J2.8, R5.1
BS_TERM: C1.1, R3.2, R4.2, R5.2
CC1: J4.A5, R1.1
CC2: J4.B5, R2.1
GND: ANT1.2, C1.2, J1.11, J1.12, J1.SH, J2.11, J2.12, J2.SH, J3.SH, J4.A1, J4.A12, J4.B1, J4.B12, J4.SH, R1.2, R2.2
LED_ECAT1: J1.9, J2.9
LED_ECAT2: J1.10, J2.10
VBUS_5V: J4.A4, J4.A9, J4.B4, J4.B9

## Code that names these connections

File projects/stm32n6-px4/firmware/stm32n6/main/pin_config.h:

/* auto-generated pin map from spec */
#define PIN_BTN_BOOT 0
#define PIN_CAN_RX 48
#define PIN_CAN_TX 49
#define PIN_I2C1_SCL 69
#define PIN_I2C1_SDA 33
#define PIN_I2C2_SCL 62
#define PIN_I2C2_SDA 63
#define PIN_LED_USER 38
#define PIN_SPI2_CS 28
#define PIN_SPI2_MISO 36
#define PIN_SPI2_MOSI 50
#define PIN_SPI2_SCK 82
#define PIN_SPI_CS 37
#define PIN_SPI_MISO 24
#define PIN_SPI_MOSI 35
#define PIN_SPI_SCK 32
#define PIN_SWCLK 14
#define PIN_SWDIO 13
#define PIN_TIM1_CH1 73
#define PIN_UART2_RX 34
#define PIN_UART2_TX 53
#define PIN_UART3_RX 74
#define PIN_UART3_TX 72
#define PIN_UART5_RX 114
#define PIN_UART5_TX 44

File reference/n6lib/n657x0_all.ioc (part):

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Mcu.Name=STM32N657X0HxQ
Mcu.Package=VFBGA264
Mcu.UserName=STM32N657X0HxQ
PA0.GPIOParameters=GPIO_Label,PinAttribute
PA0.GPIO_Label=PWR_EN
PA0.PinAttribute=Free
PA0.Signal=GPIO_Output
PA10.GPIOParameters=PinAttribute
PA10.Mode=IN11-Differential
PA10.PinAttribute=FSBL
PA10.Signal=ADC1_INP11
PA11.GPIOParameters=GPIO_Label,PinAttribute
PA11.GPIO_Label=UCPD1_VSENSE
PA11.PinAttribute=FSBL
PA11.Signal=SharedAnalog_PA11
PA13(JTMS/SWDIO).GPIOParameters=GPIO_Label,PinAttribute
PA13(JTMS/SWDIO).GPIO_Label=SWDIO
PA13(JTMS/SWDIO).Mode=Trace_Synchro_4bits_JTAG
PA13(JTMS/SWDIO).PinAttribute=FSBL
PA13(JTMS/SWDIO).Signal=DEBUG_JTMS-SWDIO
PA14(JTCK/SWCLK).GPIOParameters=GPIO_Label,PinAttribute
PA14(JTCK/SWCLK).GPIO_Label=SWCLK
PA14(JTCK/SWCLK).Mode=Trace_Synchro_4bits_JTAG
PA14(JTCK/SWCLK).PinAttribute=FSBL
PA14(JTCK/SWCLK).Signal=DEBUG_JTCK-SWCLK
PA15(JTDI).GPIOParameters=GPIO_Label,PinAttribute
PA15(JTDI).GPIO_Label=JTDI
PA15(JTDI).Mode=Trace_Synchro_4bits_JTAG
PA15(JTDI).PinAttribute=FSBL
PA15(JTDI).Signal=DEBUG_JTDI
PA5.GPIOParameters=GPIO_Label,PinAttribute
PA5.GPIO_Label=UCPD1_ISENSE
PA5.PinAttribute=Free
PA5.Signal=GPIO_Output
PA7.GPIOParameters=GPIO_Label,PinAttribute
PA7.GPIO_Label=UCPD_PWR_EN
PA7.PinAttribute=Free
PA7.Signal=GPIO_Output
PB0.GPIOParameters=GPIO_Label,PinAttribute
PB0.GPIO_Label=TRACED1
PB0.Mode=Trace_Synchro_4bits_JTAG
PB0.PinAttribute=FSBL
PB0.Signal=DEBUG_TRACED1
PB10.GPIOParameters=GPIO_Label,PinAttribute
PB10.GPIO_Label=I2C2_SCL
PB10.Mode=I2C
PB10.PinAttribute=FSBL
PB10.Signal=I2C2_SCL
PB11.GPIOParameters=GPIO_Label,PinAttribute
PB11.GPIO_Label=I2C2_SDA
PB11.Mode=I2C
PB11.PinAttribute=FSBL
PB11.Signal=I2C2_SDA
PB3.GPIOParameters=GPIO_Label,PinAttribute
PB3.GPIO_Label=TRACECLK
PB3.Mode=Trace_Synchro_4bits_JTAG
PB3.PinAttribute=FSBL
PB3.Signal=DEBUG_TRACECLK
PB5(JTDO/TRACESWO).GPIOParameters=GPIO_Label,PinAttribute
PB5(JTDO/TRACESWO).GPIO_Label=SWO
PB5(JTDO/TRACESWO).Mode=Trace_Synchro_4bits_JTAG
PB5(JTDO/TRACESWO).PinAttribute=FSBL
PB5(JTDO/TRACESWO).Signal=DEBUG_JTDO-SWO
PB6.GPIOParameters=GPIO_Label,PinAttribute
PB6.GPIO_Label=TRACED2
PB6.Mode=Trace_Synchro_4bits_JTAG
PB6.PinAttribute=FSBL
PB6.Signal=DEBUG_TRACED2
PB7.GPIOParameters=GPIO_Label,PinAttribute
PB7.GPIO_Label=TRACED3
PB7.Mode=Trace_Synchro_4bits_JTAG
PB7.PinAttribute=FSBL
PB7.Signal=DEBUG_TRACED3
PC1.GPIOParameters=GPIO_Label,PinAttribute
PC1.GPIO_Label=I2C1_SDA
PC1.Mode=I2C
PC1.PinAttribute=FSBL
PC1.Signal=I2C1_SDA
PC13.GPIOParameters=GPIO_Label,PinAttribute
PC13.GPIO_Label=USER
PC13.PinAttribute=Free
PC13.Signal=GPIO_Input
PC14-OSC32_IN(OSC32_IN).GPIOParameters=GPIO_Label,PinAttribute
PC14-OSC32_IN(OSC32_IN).GPIO_Label=OSC32_IN
PC14-OSC32_IN(OSC32_IN).Mode=LSE-External-Oscillator
PC14-OSC32_IN(OSC32_IN).PinAttribute=Free
PC14-OSC32_IN(OSC32_IN).Signal=RCC_OSC32_IN
PC15-OSC32_OUT(OSC32_OUT).GPIOParameters=GPIO_Label,PinAttribute
PC15-OSC32_OUT(OSC32_OUT).GPIO_Label=OSC32_OUT
PC15-OSC32_OUT(OSC32_OUT).Mode=LSE-External-Oscillator
PC15-OSC32_OUT(OSC32_OUT).PinAttribute=Free
PC15-OSC32_OUT(OSC32_OUT).Signal=RCC_OSC32_OUT
PD10.GPIOParameters=PinAttribute
PD10.PinAttribute=Free
PD10.Signal=GPXTI10
PD2.GPIOParameters=GPIO_Label,PinAttribute
PD2.GPIO_Label=UCPD1_INT
PD2.PinAttribute=Free
PD2.Signal=GPIO_Input
PE3.GPIOParameters=GPIO_Label,PinAttribute
PE3.GPIO_Label=TRACED0
PE3.Mode=Trace_Synchro_4bits_JTAG
PE3.PinAttribute=FSBL
PE3.Signal=DEBUG_TRACED0
PE5.GPIOParameters=GPIO_Label,PinAttribute
PE5.GPIO_Label=VCP_TX
PE5.Mode=Asynchronous
PE5.PinAttribute=FSBL
PE5.Signal=LPUART1_TX
PE6.GPIOParameters=GPIO_Label,PinAttribute
PE6.GPIO_Label=VCP_RX
PE6.Mode=Asynchronous
PE6.PinAttribute=FSBL
PE6.Signal=LPUART1_RX
PG0.GPIOParameters=GPIO_Label,PinAttribute
PG0.GPIO_Label=LED3
PG0.PinAttribute=Free
PG0.Signal=GPIO_Output
PG10.GPIOParameters=GPIO_Label,PinAttribute
PG10.GPIO_Label=LED2
PG10.PinAttribute=Free
PG10.Signal=GPIO_Output
PG8.GPIOParameters=GPIO_Label,PinAttribute
PG8.GPIO_Label=LED1
PG8.PinAttribute=Free
PG8.Signal=GPIO_Output
PH0-OSC_IN(PH0).GPIOParameters=GPIO_Label,PinAttribute
PH0-OSC_IN(PH0).GPIO_Label=OSC_IN
PH0-OSC_IN(PH0).Mode=HSE-External-Oscillator
PH0-OSC_IN(PH0).PinAttribute=Free
PH0-OSC_IN(PH0).Signal=RCC_OSC_IN
PH1-OSC_OUT(PH1).GPIOParameters=GPIO_Label,PinAttribute
PH1-OSC_OUT(PH1).GPIO_Label=OSC_OUT
PH1-OSC_OUT(PH1).Mode=HSE-External-Oscillator
PH1-OSC_OUT(PH1).PinAttribute=Free
PH1-OSC_OUT(PH1).Signal=RCC_OSC_OUT
PH9.GPIOParameters=GPIO_Label,PinAttribute
PH9.GPIO_Label=I2CA_SCL
PH9.Mode=I2C
PH9.PinAttribute=FSBL
PH9.Signal=I2C1_SCL
RCC.HSE_VALUE=24000000
board=NUCLEO-N657X0-Q
boardIOC=true

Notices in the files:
reference/n6lib/n657x0_all.ioc:
Copyright (c) 2026 STMicroelectronics. All rights reserved.
README.md:
License: Apache 2.0
parts and their libraries:
Copyright 2021 Accelerated Designs. All rights reserved.
